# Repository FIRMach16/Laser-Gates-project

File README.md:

LaserGates: A Low-Cost and accurate Timing System for Sprinters

This project aims to develop a custom-built, affordable, and precise sprint timing system from scratch ,designed specifically for track athletes and sprint coaches. The goal is to create an alternative to expensive commercial timing gates, using cheap hardware and custom software.

The system is still in active development. I’ve made this repository public to document my progress, encourage feedback, and share insights along the way. 
## Tasks:
These tasks are milestones in the project that demonstrate my learning process: 
- [Task1](Task1/) : Creating a websocket and publishing the timestamp on a button click
- [Task2](Task2/TwoGateSystem/) : A two gates system (uses button for now) that communicates VIA ESP-NOW and publish the metrics that i think are important (Time diffrence ,2 Instant Speeds for each gate) with websocket, **TODO :Measure the 2 way latencey of the ESP protocol to verify time keeping accuracy**

- [Task3](Task3/) : Android app made with Android Studio (base functionalities Complete) **TODO: Code refactoring, bug fixing, and improving UI**

- [Task4](Task4/) : PCB (Kicad) + BOM (excel) + Enclosure (software :still undecided) (PCB and BOM done waiting on components  )

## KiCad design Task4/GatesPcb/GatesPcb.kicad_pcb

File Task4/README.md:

This is a bare bone plan that I will follow to complete this Task:

- Define essential and complementary functionalites influenced by the components, PCB and the enclosure
- Design the schematic 
- Verification and testing(simulated)
- Write the Bill of Materials following best practices
- Routing
- Print the PCBs (PCBway or other platforms (price and component availablity will matter the most))
- Testing the physical PCB
- Designing the enclosures
- Printing the enclosures
- Assembly of components and eclosures 
- Pray it works
---

To document my progress in this task I will use a journal-like format where I justify the features/design choices that I'm adding.

- 27/11/2025 :

    - For the main logic I have setteled on the the esp32-s2-SOLO2 module that is low-power, single core and have wifi only (No BLE).
    - For power i will chose a LiPo 3.7v for it's ability to be recharged and it's availability, and personnaly i belive it's good choice because it will give me a good reference for other future projects.
    - For power regulation i will use a LDO (AMS1117-3.3V) as it cheap and simple enough. **Note:** because my project will need 2 functioning boards at the same time i will not include a TP4056 module to reduce cost and also to reduce risk as i know that including a LiPo charging module can significantly increase the difficulty of designing a PCB (read skill issue) however I may include it in future designs (after the first prototype works).
    - I decided add audio to the start gate to simulate the "On your marks, set ,GO!" of a real race as this will allow an athlte to measure his run time + his reaction time which will give a time closer to the one of a competition.
    - I decided to do one PCB for both the start gate and the gate, however each will have it's own specific BOM as printing the same board twice is significantly cheaper than have 2 unique designs.
- 29/11/2025:

    - After more consideration, I belive that using a Bluetooth speaker for audio is a better solution than using a built-in speaker or even designing a built-in Audio Jack here are the pros and cons of this decision:
   **Pros:**
    1. I can add range to the total distance sprinted (Speaker <-20m-> StartGate <-+30m-> EndGate)
    2. The amplification is much better than what I could design with a 3.7v battery.
    3. Most speakers nowadays use Bluetooth to play audio.
      **Cons:**
    1. I need to buy, build or find a bluetooth Speaker , to test this I'm going to use my Pc speakers, You will find the program for this [here](../Task2/BluetoothAudio).
    2. Switching between Bluetooth (For Audio Commands) and Wifi (Which will command the EndGate to start the Timer) may introduce delay in timekeeping (I want the accumulated delay to be less than 10ms). A potential workaround is to send the introduced delay value alongside the signal to start the timer, and then include it in the calculations of the sprint time.
    - What All of this mean that I need to use the ESP32 familly instead of others because it's the only one that provide the BR (basic rate) bluetooth, so no ESP32-S2.
    - Hopefully I don't change my opinion again.
- 19/12/2025:
      - At the end I decided to use a wired in speaker instead of a bluetooth one because the bluetooth present an unacceptable delay (100ms) with no way of including it in the calculations.
      - As of today the first pcb version is complete.

**Features :**
- 2 layers PCB.
- An 3.3v LDO to regulate voltage.
- A MAX98357A amplifier to use a built-in speaker with the I2S protocol.
- An esp32-solo2 as the microcontroller of the chip.
- For the power I'm planning to use a 3.7v LiPo battery which will have it's connector plugged in at the bottom right of the board.

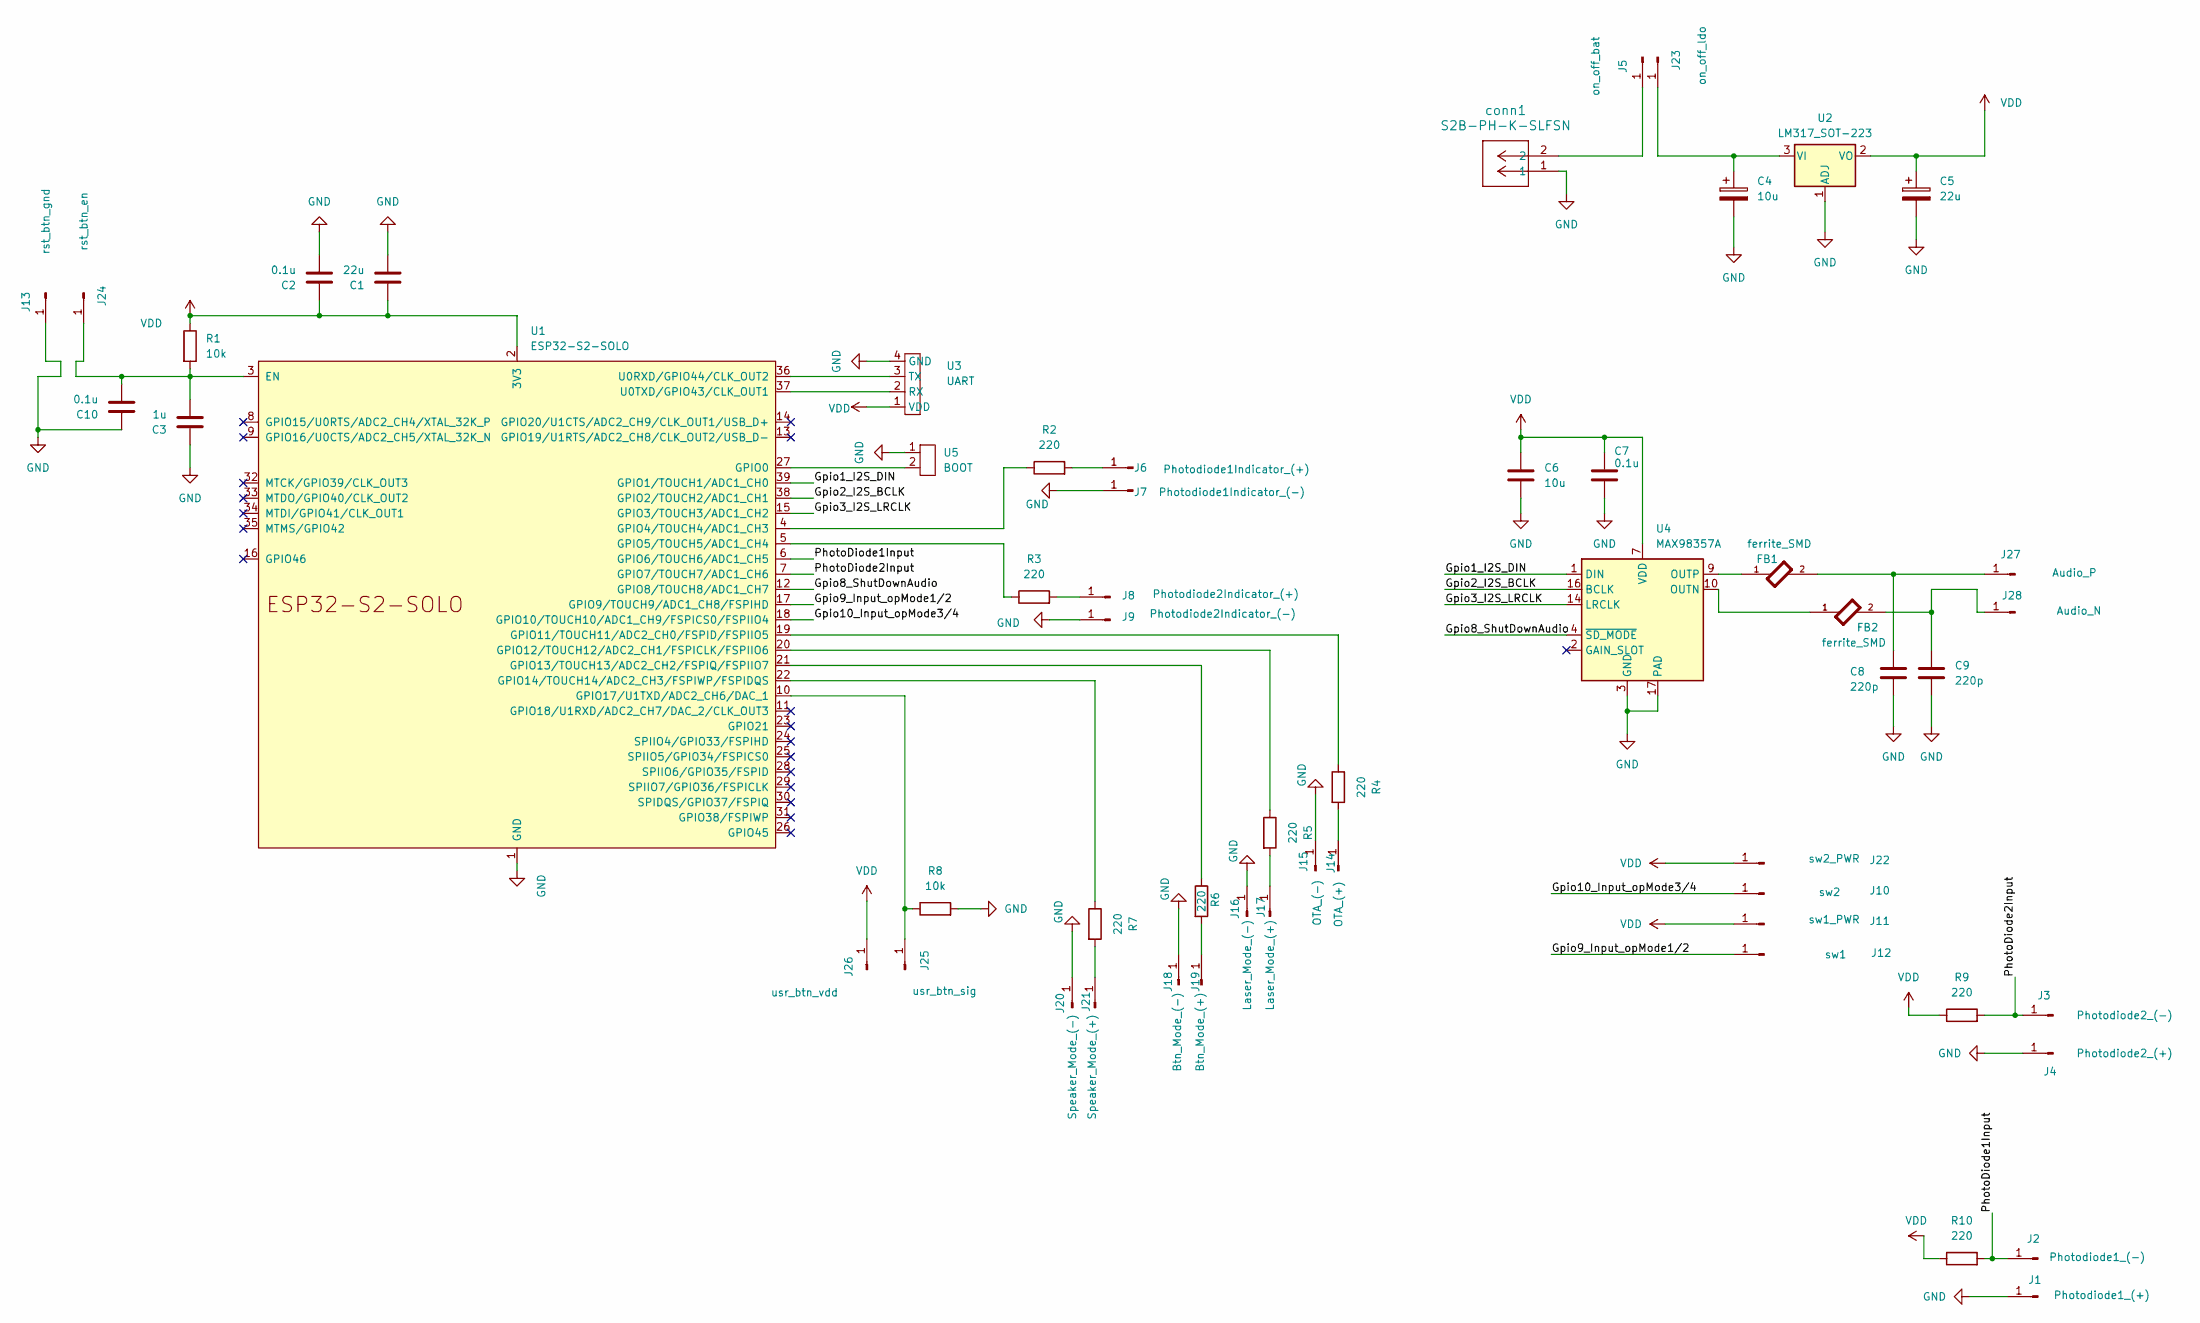
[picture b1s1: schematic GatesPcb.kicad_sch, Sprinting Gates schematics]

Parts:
C1: 22u; C_1206_3216Metric
C2, C7, C10: 0.1u; C_1206_3216Metric
C3: 1u; C_1206_3216Metric
C4: 10u; CAPMP3216X180N
C5: 22u; CAPMP3216X180N
C6: 10u; C_1206_3216Metric
C8, C9: 220p; C_1206_3216Metric
FB1, FB2: ferrite_SMD; FB_HI1206P121R-10
J1: Photodiode1_(+); +_connectorPad
J2: Photodiode1_(-); -_connectorPad
J3: Photodiode2_(-); -_connectorPad
J4: Photodiode2_(+); +_connectorPad
J5: on_off_bat; +_connectorPad
J6: Photodiode1Indicator_(+); +_connectorPad
J7: Photodiode1Indicator_(-); -_connectorPad
J8: Photodiode2Indicator_(+); +_connectorPad
J9: Photodiode2Indicator_(-); -_connectorPad
J10: sw2; -_connectorPad
J11: sw1_PWR; +_connectorPad
J12: sw1; -_connectorPad
J13: rst_btn_gnd; -_connectorPad
J14: OTA_(+); +_connectorPad
J15: OTA_(-); -_connectorPad
J16: Laser_Mode_(-); -_connectorPad
J17: Laser_Mode_(+); +_connectorPad
J18: Btn_Mode_(-); -_connectorPad
J19: Btn_Mode_(+); +_connectorPad
J20: Speaker_Mode_(-); -_connectorPad
J21: Speaker_Mode_(+); +_connectorPad
J22: sw2_PWR; +_connectorPad
J23: on_off_ldo; -_connectorPad
J24: rst_btn_en; +_connectorPad
J25: usr_btn_sig; -_connectorPad
J26: usr_btn_vdd; +_connectorPad
J27: Audio_P; +_connectorPad
J28: Audio_N; -_connectorPad
R1, R8: 10k; R_1206_3216Metric
R2, R3, R4, R5, R6, R7, R9, R10: 220; R_1206_3216Metric
U1: ESP32-S2-SOLO
U2: LM317_SOT-223; SOT-223-3_TabPin2
U3: UART; UART_Connectors_Place
U4: MAX98357A; TQFN-16-1EP_3x3mm_P0.5mm_EP1.23x1.23mm
U5: BOOT; BOOT_Connectors_Place
conn1: S2B-PH-K-SLFSN; CONN_S2B-PH-K-S_JST

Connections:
/Gpio1_I2S_DIN: U1.39 (GPIO1/TOUCH1/ADC1_CH0), U4.1 (DIN)
/Gpio2_I2S_BCLK: U1.38 (GPIO2/TOUCH2/ADC1_CH1), U4.16 (BCLK)
/Gpio3_I2S_LRCLK: U1.15 (GPIO3/TOUCH3/ADC1_CH2), U4.14 (LRCLK)
/Gpio8_ShutDownAudio: U1.12 (GPIO8/TOUCH8/ADC1_CH7), U4.4 (~SD_MODE)
/Gpio9_Input_opMode1/2: J12.1, U1.17 (GPIO9/TOUCH9/ADC1_CH8/FSPIHD)
/Gpio10_Input_opMode3/4: J10.1, U1.18 (GPIO10/TOUCH10/ADC1_CH9/FSPICS0/FSPIIO4)
/PhotoDiode1Input: J2.1, R10.2, U1.6 (GPIO6/TOUCH6/ADC1_CH5)
/PhotoDiode2Input: J3.1, R9.2, U1.7 (GPIO7/TOUCH7/ADC1_CH6)
GND: C1.1, C2.1, C3.1, C4.2, C5.2, C6.1, C7.2, C8.1, C9.1, C10.2, J1.1, J4.1, J7.1, J9.1, J13.1, J15.1, J16.1, J18.1, J20.1, R8.2, U1.1 (GND), U1.40 (GND), U1.41 (GND), U2.1 (ADJ), U3.4 (GND), U4.3 (GND), U4.11 (GND), U4.15 (GND), U4.17 (PAD), U5.1, conn1.1
unnamed: J5.1, conn1.2
unnamed: J6.1, R2.2
unnamed: J8.1, R3.2
unnamed: J14.1, R4.2
unnamed: J17.1, R5.2
unnamed: J19.1, R6.2
unnamed: J21.1, R7.2
unnamed: C4.1, J23.1, U2.3 (VI)
unnamed: C3.2, C10.1, J24.1, R1.2, U1.3 (EN)
unnamed: J25.1, R8.1, U1.10 (GPIO17/U1TXD/ADC2_CH6/DAC_1)
unnamed: C8.2, FB1.2, J27.1
unnamed: C9.2, FB2.2, J28.1
unnamed: U1.27 (GPIO0), U5.2
unnamed: R2.1, U1.4 (GPIO4/TOUCH4/ADC1_CH3)
unnamed: R3.1, U1.5 (GPIO5/TOUCH5/ADC1_CH4)
unnamed: R4.1, U1.19 (GPIO11/TOUCH11/ADC2_CH0/FSPID/FSPIIO5)
unnamed: R5.1, U1.20 (GPIO12/TOUCH12/ADC2_CH1/FSPICLK/FSPIIO6)
unnamed: R6.1, U1.21 (GPIO13/TOUCH13/ADC2_CH2/FSPIQ/FSPIIO7)
unnamed: R7.1, U1.22 (GPIO14/TOUCH14/ADC2_CH3/FSPIWP/FSPIDQS)
unnamed: U1.36 (U0RXD/GPIO44/CLK_OUT2), U3.3 (TX)
unnamed: U1.37 (U0TXD/GPIO43/CLK_OUT1), U3.2 (RX)
unnamed: FB2.1, U4.10 (OUTN)
unnamed: FB1.1, U4.9 (OUTP)
VDD: C1.2, C2.2, C5.1, C6.2, C7.1, J11.1, J22.1, J26.1, R1.1, R9.1, R10.1, U1.2 (3V3), U2.2 (VO), U3.1 (VDD), U4.7 (VDD), U4.8 (VDD)

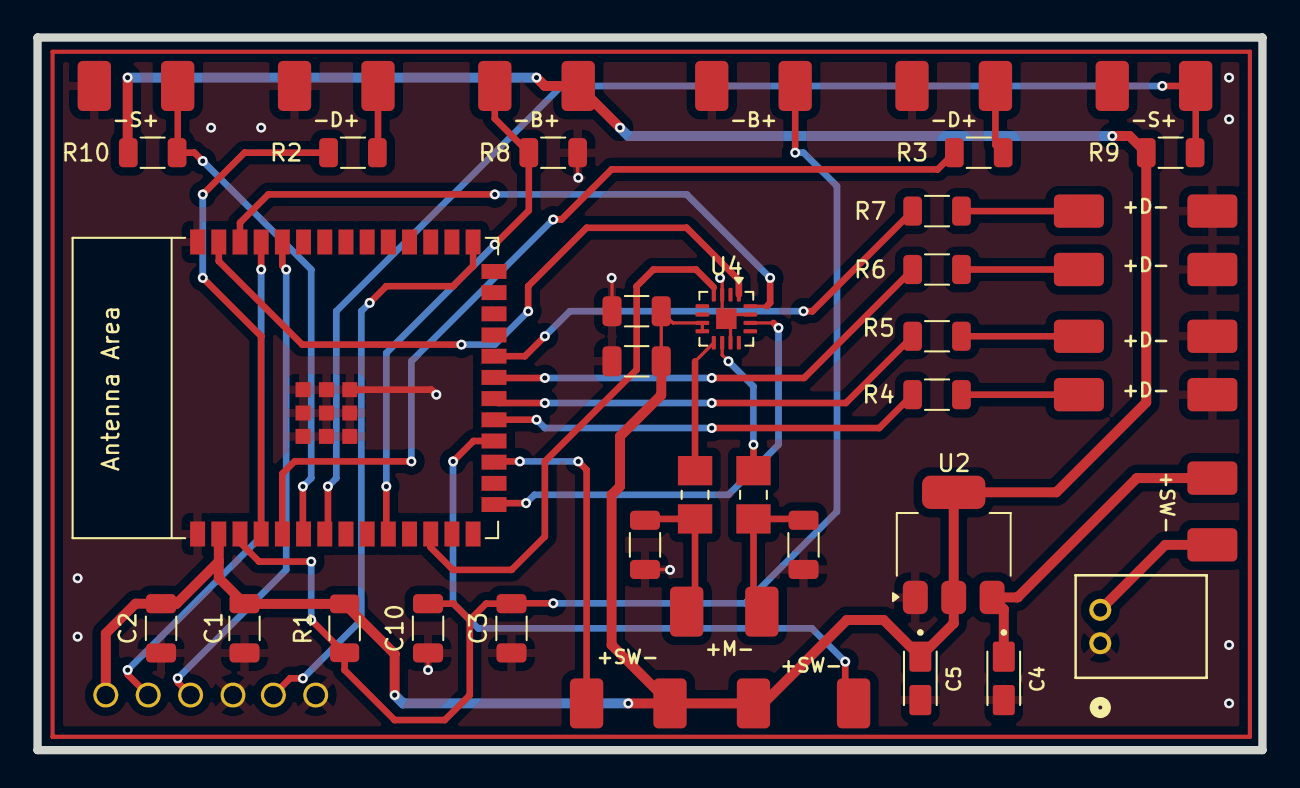
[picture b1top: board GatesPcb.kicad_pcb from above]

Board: 2 copper layers, 73.4 x 42.7 mm, 56 parts (0 on the bottom side), 33 nets.

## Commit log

2025-07-30 TaskOne (sed Timestamp over websocket)
2025-07-30 correction
2025-08-08 Create README.md
    initial readme
2025-08-08 TaskOne readme
2025-08-10 End gate server content
2025-08-12 TaskTwo DashBoard
2025-09-08 Two Gates System
2025-09-08 Doc of 2 gate system
2025-09-08 Correction of task one
2025-09-10 Task Three Initial commit
2025-09-10 Renaming Tasks
2025-09-13 first sprint
2025-09-13 "first sprint"
2025-09-18 Update for the planning of the app
2025-09-19 Second Sprint
2025-09-21 Sprint2 documentation
2025-09-21 third sprint
2025-09-21 New Planning
2025-09-21 Sprint 2 +3 refrences
2025-09-25 Sprint4
2025-09-25 Sprint 4 refrence
2025-10-01 Sprint 5
2025-10-01 Sprint 5 doc
2025-10-03 demo videos refrenced
2025-10-03 Sprint 5 demo video
2025-10-03 update task3 readme
2025-10-09 Progression UI with Compose , Next: db interaction
2025-10-09 timer icon in android app drawable
2025-10-18 ProgressionViewModel + DataBase Unit Testing (lacks ui update)
2025-10-24 Sprint6 complete HOORAY!! plus UNIT testing for DB operations
2025-10-25 Sprint6 doc
2025-10-25 Switching to Linux XD, bye microsoft
2025-10-25 Fix Non working Doc link (sprint6 related)
2025-10-25 fixing Sprint6 doc
2025-11-04 Sprint 7 UI lacks data interaction and a for loop in the lazy Column
2025-11-04 main read me update
2025-11-07 Navigation Working next step DB interaction with SprintsUI
2025-11-08 Sprint7 complete!
2025-11-08 Sprint7 doc in readme
2025-11-18 Sprint8 UI complete, calculating the control points position was a waste of time
2025-11-18 Sprint8 Finished Will add docs Later
2025-11-18 Sprint8 doc
2025-11-20 Sprint9 complete App main functionalities complete movig to pcb
2025-11-23 bare bone plan of TASK4
2025-11-23 small update
2025-11-27 Task4 first choices and schematics
2025-11-28 grammar fixes in task4 readme
2025-11-29 new plan for the product (task4)
2025-11-29 readme.md layout fix
2025-12-03 Task2 : Bluetooth Audio
2025-12-03 Task2 readme
2025-12-19 finished first pcb hopefully it works ...
2025-12-19 update on pcb progress
2025-12-19 pcb routing correction
